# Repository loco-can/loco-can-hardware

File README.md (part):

# Loco-CAN Hardware
**Development version 3.x**

The new version 3.x marks the switch from the Atmega MCUs to the ESP32 series from the Chinese manufacturer [Espressif](https://www.espressif.com). In addition to integrated Bluetooth and WiFi functionality, the CAN controller is also already built in, making the modules even smaller.

The first module is a complete 4-quadrant motor driver for 80 amps motor current, which can be operated directly on the CAN bus.

Version 3.x is fully compatible with all other versions.

**Current version V2.2**

The software is managed in the [Loco-CAN-Software](https://github.com/Loco-can/Loco-can-software) repository.

The Loco-CAN project is an electronic control system for the large passenger-carrying garden railway. The communication is based on the CAN bus, which is used in the automotive industry and in automation. The serial signal transmission is very robust and supports multiple masters and multiple slaves.

The modular system consists of different components with specialized tasks. For example, there are modules for operating, for controlling motor controls, light switch modules or sensors for current and voltage measurement or speed values. Actuators that are addressed by a servo module can even be used to control diesel engines or gearboxes.

Due to the flexibility of the CAN bus, additional modules can easily be connected without having to change the existing structure.

The system is not only intended for networking within a traction vehicle, but can also be routed through the train via a four-pole cable. This means that not only can control consoles be connected at any point in the train, but also, for example, lights in wagons can be operated.

The system is still under developement. The CAN-specification is defined but can be extended. Board designs are available in different versions, due to the process of evolvement. Besides bugs in the board design details like the pinout of the program interface differ between the versions.

# Version
The current development of the system is based on version 2.x. It combines the microcontroller and the CAN bus connector with the specialized function on one board. Due to the use of SMD components, the modules are significantly smaller than in old 1.x versions.

With the universal module, a version with an expansion bus is also available.

## Wired units
| Unit            | Type            |
|:----------------|:----------------|
| Processor       | Atmega 328P     |
| CAN-Controller  | MCP 2515        |
| CAN-Transceiver | MCP 2551        |

## Wireless units
| Unit            | Type            |
|:----------------|:----------------|
| Processor       | ESP32           |
| CAN-Controller  | integrated      |
| CAN-Transceiver | MCP 2551        |

# Connectors
The following connectors for the basic IOs are universal used by all modules if needed. The information includes the technical specifications for the connectors and the electrical assignment.

## CAN bus
The CAN-bus is found on all modules, even the WIFI. It connects all modules and provides both communication and supply.

**4-pin 2x2**
Plug: MATE-N-LOK 794617-4
Jack: MATE-N-LOK 3-794618-4

| pin | usage                      |
|:---:|:---------------------------|
| 1   | GND                        |
| 2   | CAN-L                      |
| 3   | CAN-H                      |
| 4   | +6-30 Volt / max. 5 Ampere |

### Loco interconnection
**4-pin Mini-XLR**
The Mate-N-LOK connectors are used for internal wiring only. 4-pin MINI-XLR connectors are used to couple vehicles together. The plugs are robust, but at the same time small enough to allow model-like housings around the plugs. The pin assignment matches the internal connectors. On the vehicle the female connectors are used.

| pin | usage                      |
|:---:|:---------------------------|
| 1   | +6-30 Volt / max. 5 Ampere |
| 2   | CAN-L                      |
| 3   | CAN-H                      |
| 4   | GND                        |

### Cables
The four-pole CAN bus cables should have a minimum cross-section of 0.34mm² in order to withstand the maximum current of five amperes.

Recommended cable: UNITRONIC® ROBUST 4x0.34 black

## Pulse
Used for speed or rpm measurement.

**2-pin horizontal**
Plug: MATE-N-LOK 2-1445055-2
Jack: MATE-N-LOK 1445022-2

| pin | usage |
|:---:|:------|
| 1   | Pulse |
| 2   | GND   |

## Power
Supply input for the Loco-system.

**2-pin vertical**
Plug: MATE-N-LOK 794617-2
Jack: MATE-N-LOK 3-794618-2

| pin | usage  |
|:---:|:-------|
| 1   | +6-30V |
| 2   | GND    |

# ICP SDI pads
To flash the bootloader on Atmega chips latter versions provide four pads to access the SDI port of the MCU and a reset signal. A jumper in the CS line between the MCU and the CAN controller has to be open for the flash process and closed for normal operation.

The hardware versions with the SDI pads before 2.2 are marked with a letter s at the end of the version string.

ICP-Interface
| pin | usage |
|:----|:------|
| 1   | SCK   |
| 2   | SI    |
| 3   | SO    |
| 4   | RST   |

# Modules
All modules, except Loco-Single, are equipped with two 4-pin CAN connectors. The following modules are available or in developement:

## Interface definitions
The pinout of the FTDI interface for flashing new software differs in the early versions. The standard pinout will be implemented in all revisions, divergent pinouts are listed with the version descriptions.

All versions are compatible on the CAN-bus, the differences are only in the expansion ports.

Standard FTDI Interface to flash software updates
| pin | usage        | cable  |
|:----|:-------------|--------|
| 1   | **1 DTS**    | yellow |
| 2   | **2 RX**     | braun  |
| 3   | **3 TX**     | white  |
| 4   | **4 3V3/5V** | green  |
| 5   | **GND**      | GND    |

# Loco-Motor
With the Loco-Motor module all types of power drivers can be controlled via the CAN bus. The setup of the motor software can be adapted to a wide variety of motor control drivers. With the additional light and horn outputs a locomotive control can be set up with a control and a motor module.

## V2.1a/V2.2
The versions mainly differ in the pinout of the FDTI-interface.

### Motor driver
Plug: MATE-N-LOK 1-794617-0
Jack: MATE-N-LOK 4-794618-0

| pin | usage       | pin | usage       |
|:----|:------------|:----|:------------|
| 1   | +bus IN     | 2   | Light       |               
| 3   | DRIVE       | 4   | HORN        |
| 5   | BREAK       | 6   | MOTOR VOLT+ |
| 7   | FORWARD     | 8   | MOTOR VOLT- |
| 9   | REVERSE     | 10  | GND         |

Pins 6 and 8 are connected to the motor output to sense the voltage. Drive and break outputs provide a PWM signal to drive the power output stage.

### FTDI Interface
| V2.1a    | V2.1b     |
|:---------|:----------|
| 1 DTS    | **1 DTS** |
| 2 **TX** | **2 RX**  |
| 3 **RX** | **3 TX**  |
| 4 3V3    | **4 3V3** |
| 5 GND    | **5 GND** |

# Loco-Switch
With the switch module different lights and other devices can be switched. Each output can drive up to 3 Ampere, when using the external +bus input with the version greater V2.1. With the V2.0 only the maximum output current of the CAN-bus can be used.

## Setup
With the base setup the module is configurated to use the light messages to set the outputs. A setup to react on every message for each output increases the flexibility. As an example four outputs can be used for different lights, one output to drive a horn and the last to activate an pantograph.

###CAN light stati
The can protocol supports eight light stati in out byte, that can be mapped to the six output lines in the module setup. To activate a status, the corresponding bit has to be set to 1.

	bits     7      6      5      4      3      2      1      0
	       	main  train   cab   instr   back    high   low   posit
	       	------------------------------------------------------
	main:	main light switch
	train:	train lights
	cab:	cabine light
	instr:	instrument light
	back:	back light
	high:	bright spot light
	low:	low spot light
	posit:	position light

A common current sensor returns the overall consumption of all outputs.

The versions differ in the pinout of the output connector and the FDTI-interface.

## Output connector
Degson DG308-2.54-08P-14-00AH
or
JST XH

## Hardware version V2.0
| pin | usage      |
|:----|:-----------|
| 1   | Output 1   |
| 2   | Output 2   |
| 3   | Output 3   |
| 4   | Output 4   |
| 5   | Output 5   |
| 6   | Output 6   |
| 7   | GND        |

## Hardware version V2.1a/V2.2
| pin | usage      |
|:----|:-----------|
| 1   | +bus       |
| 2   | Output 1   |
| 3   | Output 2   |
| 4   | Output 3   |
| 5   | Output 4   |
| 6   | Output 5   |
| 7   | Output 6   |
| 8   | GND        |

The switching module can switch up to 3 amps per output. Both resistive and inductive loads can be switched. If the current is taken from the bus, make sure that the total consumption of the system does not exceed the limit of 5 amperes.

If all outputs are operated with 3 amps, a separate supply line must be laid from the positive pole of the battery to the loads and from the negative pole of the battery to the GND connection of the switching output. The value of the maximum current must be adjusted in the configuration of the module.

### FTDI Interface
| V2.1     | V2.1a     |
|:---------|:----------|
| 1 DTS    | **1 DTS** |
| 2 **TX** | **2 RX**  |
| 3 **RX** | **3 TX**  |
| 4 3V3    | **4 3V3** |
| 5 GND    | **5 GND** |

# Loco-Single
A tiny module with only one fix wired CAN connector and one current controlled output for a single LED light. It can be used for intelligent back lights. In this case, a backlight heartbeat status can detect the train integrity.

# Loco-Sensor
The sendor module provides four voltage inputs and a current measurement up to 30 Ampere. In addition a speed/pulse input is provided.

## Hardware version V2.1/V2.1a/V2.1a-s
The versions differ in the pinout of the FDTI-interface. Both versions V2.1a and V2.1a-s offers the SDI pads.

### Voltage
The pins can provide absolute values reffered to GND, or relative values between two pins, depending on the module setup.

| pin | usage     |
|:----|:----------|
| 1   | Voltage 1 |
| 2   | Voltage 2 |
| 3   | Voltage 3 |
| 4   | Voltage 4 |

### Current
The current measurement connectors are thwo 6mm holes outside of the casing. The direction of the current is provided as positive or negative values. The ratio of the positive direction to the connection on the pins, can be set in the setup.

### Speed/pulse
See in the Connector section below.

### FTDI Interface
| V2.1     | V2.1a     |
|:---------|:----------|
| 1 DTS    | **1 DTS** |
| 2 **TX** | **2 RX**  |
| 3 **RX** | **3 TX**  |
| 4 3V3    | **4 3V3** |
| 5 GND    | **5 GND** |

## Loco-Servo
The module provides four analog model servo outputs. The power for all servos must not exceed 900mA. If more power is needed, the 5 Volt for the servo motors must be supplied by an external voltage regulator.

The values for each servo motor position can be mapped to each analog value of CAN messages. The received values are mapped using input min and max settings and output min and max values. Reverse actions are reached by setting the output mapping values in a reversed order (forward: input 0-1024 => output 100-170, reverse: input 0-1024 => output: 180-100).

### V2.0/V2.2
The versions only differ in the pinout of the FDTI-interface.

### 12-pin Servo Output
Plug: MATE-N-LOK 1-794617-2
Jack: MATE-N-LOK 4-794618-2

| Row 1     | Row 2      |
|:----------|:-----------|
| 1 Servo-1 | 7 Servo-3  |
| 2 +5V     | 8 +5V      |
| 3 GND     | 9 GND      |
| 4 Servo-2 | 10 Servo-4 |
| 5 +5V     | 11 +5V     |
| 6 GND     | 12 GND     |

### FTDI Interface
| V2.0     | V2.2  |
|:---------|:----------|
| 1 DTS    | **1 DTS** |
| 2 **TX** | **2 RX**  |
| 3 **RX** | **3 TX**  |
| 4 3V3    | **4 3V3** |
| 5 GND    | **5 GND** |

## Loco-Universal
These modules offer an unallocated connector for universal use. 

### V1.0
The first prototype board using DIL packages and JST-PH connectors for the CAN-bus. **Although this version is compatible with the system, it is no longer supported!**

**Extension bus: 10x1 pins**
| pin         | usage        |
|:------------|:-------------|
| 1  VCC      |              |
| 2  D9 (PWM) | METER_AMP    |
| 3  D8       | METER_VOLT   |
| 4  D7       | STATUS_GREEN |
| 5  D6 (PWM) | STATUS_RED   |
| 6  A0       | ANALOG_DRIVE |
| 7  A1       | MAINS_SWITCH |
| 8  A2       | DIR_SWITCH   |
| 9  A3       | LIGHT_SWITCH |
| 10 GND      |              |

### V1.2
The second prototype board using DIL packages and an bigger extension bus. It was never produced. **Although this version is compatible with the system, it is no longer supported!**

**Extension bus: 8x2 pins**
| pin         | usage             | pin         | usage              |
|:------------|:------------------|:------------|:-------------------|
| 1  VCC      |                   | 2  D2       |                    | 
| 3  A5       |                   | 4  D3 (PWM) |                    |
| 5  A4       |                   | 6  D4       |                    |
| 7  A3       |                   | 8  D5 (PWM) |                    |
| 8  A2       |                   | 10 D6 (PWM) | STATUS_RED         |
| 11 A1       |                   | 12 D7       | STATUS_GREEN       |
| 13 A0       |                   | 14 D8       | METER_VOLT (Servo) |
| 15 D9 (PWM) | METER_AMP (Servo) | 16 GND      |                    |

**big extension bus version: 9x2 pins**
| pin         | usage             | pin         | usage              |
|:------------|:------------------|:------------|:-------------------|
| 17  +bus    |                   | 18 GND      |                    | 

### FTDI Interface
Both versions provide the default FTDI pinout.
| pin | usage     |
|:----|:----------|
| 1   | **1 DTS** |
| 2   | **2 RX**  |
| 3   | **3 TX**  |
| 4   | **4 3V3** |
| 5   | **GND**   |

### V2.x
From version 2.x the universal board is pin compatible with the WIFI universal board.

| **IO 1**           | **IO 2**             |
|:-------------------|:---------------------|
| **9x1 pins**       | **5+4x1 pins**       |
| 1 +5V              | 1 +bus               |
| 2 D2               | 2 A5                 |
| 3 D3               | 3 A4                 |
| 4 D4               | 4 A3                 |
| 5 D5               | 5 A2                 |
| 6 D6               |                      |
| 7 D7               | 1 A1                 |
| 8 D8               | 2 A0                 |
| 9 GND              | 3 D9                 |
|                    | 4 GND                |

### FTDI Interface
The version provide the default FTDI pinout. To flash a new software version, pin 3 of the 5-pin IO 2 must be connected to GND before power up.

| pin | usage     |
|:----|:----------|
| 1   | **1 DTS** |
| 2   | **2 RX**  |
| 3   | **3 TX**  |
| 4   | **4 3V3** |
| 5   | **GND**   |

The +bus connection can either be used to power the CAN bus from an outside source, like a motor driver or in reverse provide an outside device with the bus supply of 6 to 30 Volts. In the different use cases the diode D2 has to be swapped regarding the printed direction for in or out on the pcb.

## Loco-WIFI (universal)
The Loco-WIFI is a universal module with two extension busses besides the two CAN connectors. It can establish a wireless connection via WIFI and Bluetooth. 

### V2.1
The ESP32 boards are shipped with a bootloader and do not need the SPI flash pads.

| **IO 1**           | **IO 2**             |
|:-------------------|:---------------------|
| **9x1 pins**       | **5+4x1 pins**       |
| 1 +3,3V            | 1 VCC (12V)          |
| 2 IO27             | 2 IO4                |
| 3 IO26             | 3 IO0 (GND to Flash) |
| 4 IO25             | 4 IO2                |
| 5 IO33             | 5 IO15               |
| 6 IO32             |                      |
| 7 IO35             | 1 IO13               |
| 8 IO34             | 2 IO12               |
| 9 GND              | 3 IO14               |
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
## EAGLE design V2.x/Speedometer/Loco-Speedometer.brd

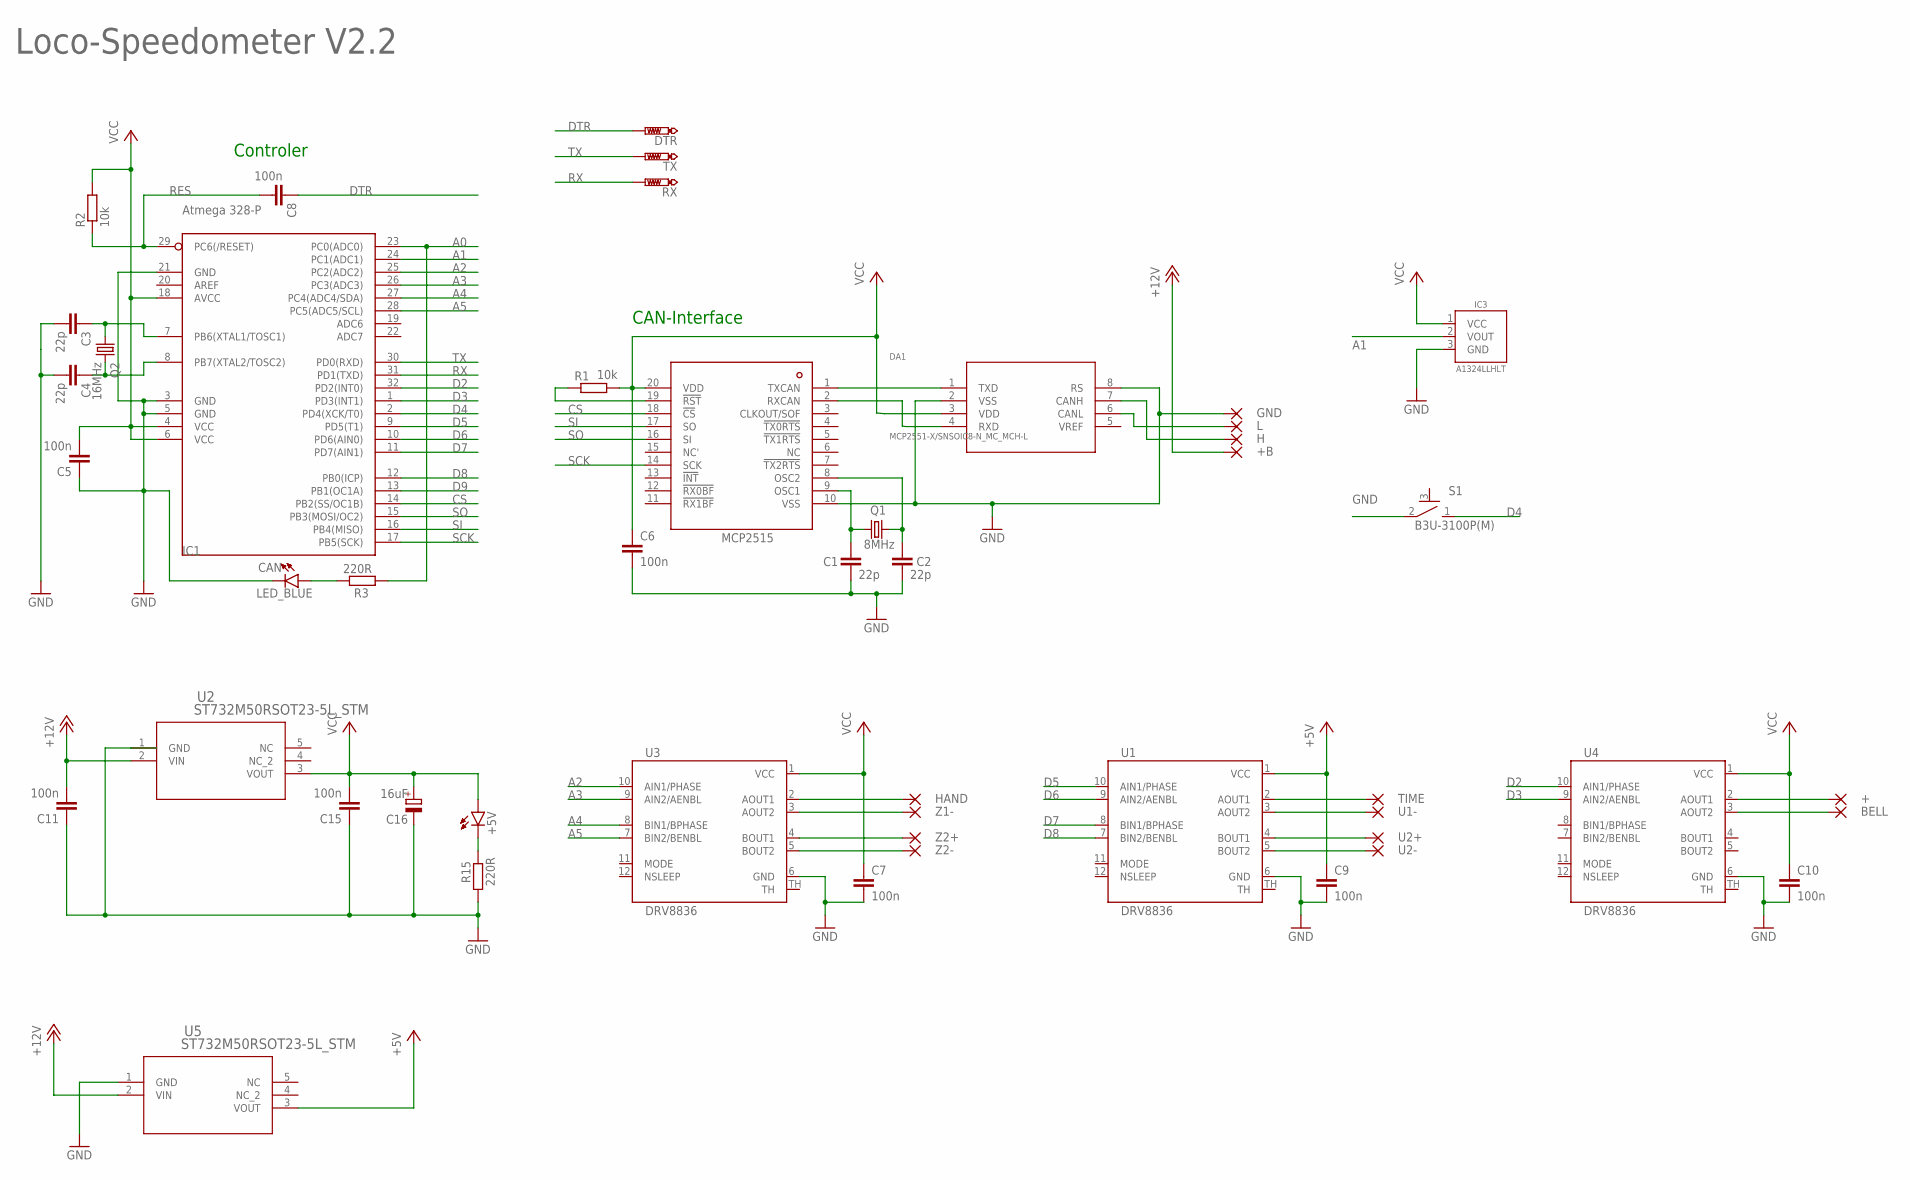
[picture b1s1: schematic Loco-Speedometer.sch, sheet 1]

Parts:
+: SMD1; SMD1,27-1,90
+5V: LEDCHIP-LED0603; CHIP-LED0603
+B: SMD1; SMD1,27-1,90
BELL: SMD1; SMD1,27-1,90
C1, C2, C3, C4: 22p; C0402K
C5, C6, C7, C8, C9, C10, C11, C15: 100n; C0402K
C16: 16uF; A/3216-18W
CAN: LED_BLUE; LEDC1608X39N_B
DA1: MCP2551-X/SNSOIC8-N_MC_MCH-L; SOIC8-N_MC_MCH-L
DTR: PTR1B1,27; B1,27
GND: SMD1; SMD1,27-1,90
H: SMD1; SMD1,27-1,90
HAND: SMD1; SMD1,27-1,90
IC1: Atmega 328-P; TQFP32-08
IC2: MCP2515; TSSOP20
IC3: A1324LLHLT; SOT95P285X113-3N
L: SMD1; SMD1,27-1,90
Q1: 8MHz; 5.0X3.2_2
Q2: 16MHz; 5.0X3.2_2
R1, R2: 10k; R0402
R3, R15: 220R; R0402
RX: PTR1B1,27; B1,27
S1: B3U-3100P(M)
TIME: SMD1; SMD1,27-1,90
TX: PTR1B1,27; B1,27
U1, U3, U4: DRV8836; 12WSON
U1-, U2+, U2-: SMD1; SMD1,27-1,90
U2, U5: ST732M50RSOT23-5L_STM; SOT23-5L_STM
Z1-, Z2+, Z2-: SMD1; SMD1,27-1,90

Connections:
+5V: C9.1, U1.1 (VCC), U5.3 (VOUT)
+12V: +B.1, C11.2, U2.2 (VIN), U5.2 (VIN)
A0: IC1.23 (PC0(ADC0)), R3.1
A1: IC1.24 (PC1(ADC1)), IC3.2 (VOUT)
A2: IC1.25 (PC2(ADC2)), U3.10 (AIN1/PHASE)
A3: IC1.26 (PC3(ADC3)), U3.9 (AIN2/AENBL)
A4: IC1.27 (PC4(ADC4/SDA)), U3.8 (BIN1/BPHASE)
A5: IC1.28 (PC5(ADC5/SCL)), U3.7 (BIN2/BENBL)
CAN-H: DA1.7 (CANH), H.1
CAN-L: DA1.6 (CANL), L.1
CAN-OCC1: C1.1, IC2.9 (OSC1), Q1.1
CAN-OCC2: C2.1, IC2.8 (OSC2), Q1.2
CS: IC1.14 (PB2(SS/OC1B)), IC2.18 (!CS)
D2: IC1.32 (PD2(INT0)), U4.10 (AIN1/PHASE)
D3: IC1.1 (PD3(INT1)), U4.9 (AIN2/AENBL)
D4: IC1.2 (PD4(XCK/T0)), S1.1 (2)
D5: IC1.9 (PD5(T1)), U1.10 (AIN1/PHASE)
D6: IC1.10 (PD6(AIN0)), U1.9 (AIN2/AENBL)
D7: IC1.11 (PD7(AIN1)), U1.8 (BIN1/BPHASE)
D8: IC1.12 (PB0(ICP)), U1.7 (BIN2/BENBL)
D9: IC1.13 (PB1(OC1A))
DTR: C8.1, DTR.TP
GND: C1.2, C2.2, C3.2, C4.2, C5.1, C6.2, C7.2, C9.2, C10.2, C11.1, C15.1, C16.-, CAN.1 (C), DA1.2 (VSS), DA1.8 (RS), GND.1, IC1.3 (GND), IC1.5 (GND), IC1.21 (GND), IC2.10 (VSS), IC3.3 (GND), R15.1, S1.2 (1), U1.6 (GND), U2.1 (GND), U3.6 (GND), U4.6 (GND), U5.1 (GND)
unnamed: CAN.2 (A), R3.2
unnamed: IC2.19 (!RST), R1.1
unnamed: C7.1, U3.1 (VCC)
unnamed: C3.1, IC1.7 (PB6(XTAL1/TOSC1)), Q2.1
unnamed: C4.1, IC1.8 (PB7(XTAL2/TOSC2)), Q2.2
unnamed: +5V.C, R15.2
RES: C8.2, IC1.29 (PC6(/RESET)), R2.1
RX: IC1.31 (PD1(TXD)), RX.TP
RXCAN: DA1.4 (RXD), IC2.2 (RXCAN)
SCK: IC1.17 (PB5(SCK)), IC2.14 (SCK)
SI: IC1.16 (PB4(MISO)), IC2.17 (SO)
SO: IC1.15 (PB3(MOSI/OC2)), IC2.16 (SI)
TX: IC1.30 (PD0(RXD)), TX.TP
TXCAN: DA1.1 (TXD), IC2.1 (TXCAN)
U1+: TIME.1, U1.2 (AOUT1)
U1+1: +.1, U4.2 (AOUT1)
U1-: U1.3 (AOUT2), U1-.1
U1-1: BELL.1, U4.3 (AOUT2)
U2+: U1.4 (BOUT1), U2+.1
U2-: U1.5 (BOUT2), U2-.1
VCC: +5V.A, C5.2, C6.1, C10.1, C15.2, C16.+, DA1.3 (VDD), IC1.4 (VCC), IC1.6 (VCC), IC1.18 (AVCC), IC2.20 (VDD), IC3.1 (VCC), R1.2, R2.2, U2.3 (VOUT), U4.1 (VCC)
Z1+: HAND.1, U3.2 (AOUT1)
Z1-: U3.3 (AOUT2), Z1-.1
Z2+: U3.4 (BOUT1), Z2+.1
Z2-: U3.5 (BOUT2), Z2-.1

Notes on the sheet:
CAN-Interface
Controler
Loco-Speedometer V2.2

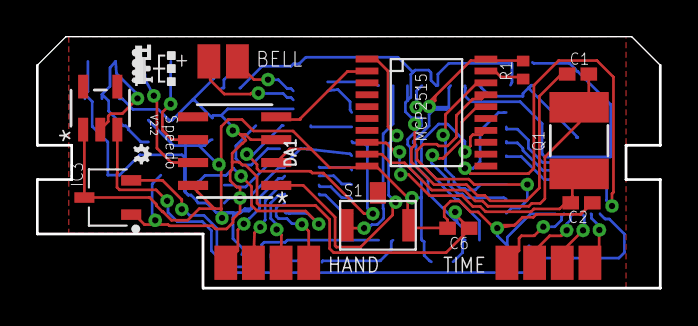
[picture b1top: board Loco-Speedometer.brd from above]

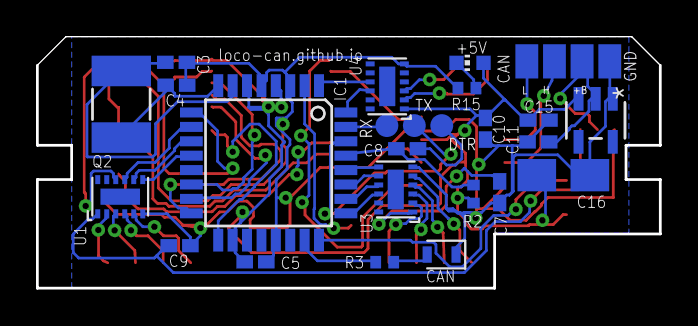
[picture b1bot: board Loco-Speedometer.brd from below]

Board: 2 copper layers, 34.6 x 14.0 mm, 48 parts (28 on the bottom side), 47 nets.

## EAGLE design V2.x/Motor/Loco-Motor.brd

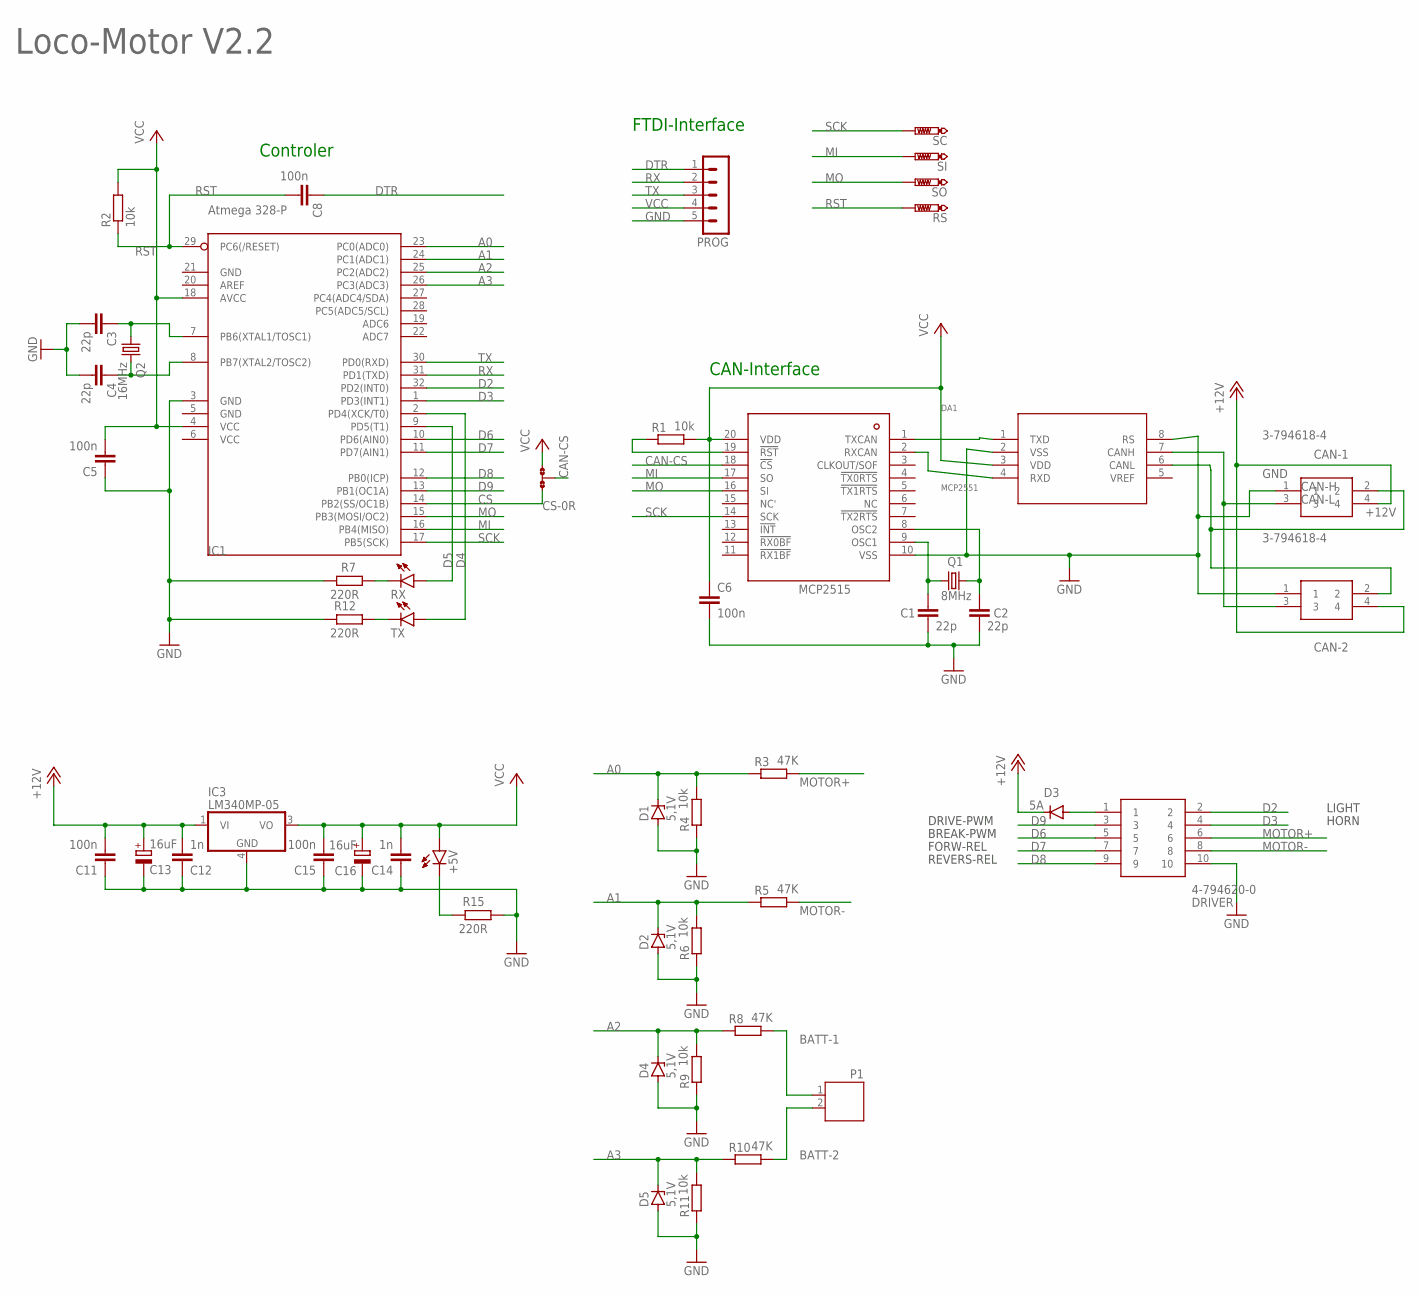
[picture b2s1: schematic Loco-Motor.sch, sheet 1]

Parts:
+5V: LEDCHIP-LED0603; CHIP-LED0603
C1, C2, C3, C4: 22p; C0402K
C5, C6, C8, C11, C15: 100n; C0402K
C12, C14: 1n; C0402K
C13, C16: 16uF; A/3216-18W
CAN-1, CAN-2: 3-794618-4
CS: 0R-JUMPA; A0R-JMP
D1, D2, D4, D5: 5,1V; SOD80C
D3: 5A; DO214AA
DA1: MCP2551; SOIC8-N_MC_MCH
DRIVER: 4-794620-0; 47946200
IC1: Atmega 328-P; TQFP32-08
IC2: MCP2515; TSSOP20
IC3: LM340MP-05; SOT223
P1: JST-PH2
PROG: MA05-1
Q1: 8MHz; HC49/S
Q2: 16MHz; HC49/S
R1, R2: 10k; R0805
R3, R5, R8, R10: 47K; MINI_MELF-0102W
R4, R6, R9, R11: 10k; MINI_MELF-0102W
R7, R12, R15: 220R; R0805
RS: PTR1B1,27; B1,27
RX: LEDCHIP-LED0603; CHIP-LED0603
SC: PTR1B1,27; B1,27
SI: PTR1B1,27; B1,27
SO: PTR1B1,27; B1,27
TX: LEDCHIP-LED0603; CHIP-LED0603

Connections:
+12V: C11.2, C12.2, C13.+, CAN-1.4, CAN-2.4, D3.C, IC3.1 (VI)
A0: D1.C, IC1.23 (PC0(ADC0)), R3.1, R4.2
A1: D2.C, IC1.24 (PC1(ADC1)), R5.1, R6.2
A2: D4.C, IC1.25 (PC2(ADC2)), R8.1, R9.2
A3: D5.C, IC1.26 (PC3(ADC3)), R10.1, R11.2
BATT-1: P1.1, R8.2
BATT-2: P1.2, R10.2
CAN-CS: CS.2, IC2.18 (!CS)
CAN-H: CAN-1.3, CAN-2.3, DA1.7 (CANH)
CAN-L: CAN-1.2, CAN-2.2, DA1.6 (CANL)
CAN-OCC1: C1.1, IC2.9 (OSC1), Q1.1
CAN-OCC2: C2.1, IC2.8 (OSC2), Q1.2
CS: CS.3, IC1.14 (PB2(SS/OC1B))
D2: DRIVER.2, IC1.32 (PD2(INT0))
D3: DRIVER.4, IC1.1 (PD3(INT1))
D4: IC1.2 (PD4(XCK/T0)), TX.A
D5: IC1.9 (PD5(T1)), RX.A
D6: DRIVER.5, IC1.10 (PD6(AIN0))
D7: DRIVER.7, IC1.11 (PD7(AIN1))
D8: DRIVER.9, IC1.12 (PB0(ICP))
D9: DRIVER.3, IC1.13 (PB1(OC1A))
DTR: C8.1, PROG.1
GND: C1.2, C2.2, C3.2, C4.2, C5.1, C6.2, C11.1, C12.1, C13.-, C14.1, C15.1, C16.-, CAN-1.1, CAN-2.1, D1.A, D2.A, D4.A, D5.A, DA1.2 (VSS), DA1.8 (RS), DRIVER.10, IC1.3 (GND), IC1.5 (GND), IC1.21 (GND), IC2.10 (VSS), IC3.4 (GND), PROG.5, R4.1, R6.1, R7.2, R9.1, R11.1, R12.2, R15.1
MI: IC1.16 (PB4(MISO)), IC2.17 (SO), SI.TP
MO: IC1.15 (PB3(MOSI/OC2)), IC2.16 (SI), SO.TP
MOTOR+: DRIVER.6, R3.2
MOTOR-: DRIVER.8, R5.2
unnamed: D3.A, DRIVER.1
unnamed: R7.1, RX.C
unnamed: R12.1, TX.C
unnamed: IC2.19 (!RST), R1.1
unnamed: C3.1, IC1.7 (PB6(XTAL1/TOSC1)), Q2.1
unnamed: C4.1, IC1.8 (PB7(XTAL2/TOSC2)), Q2.2
unnamed: +5V.C, R15.2
RST: C8.2, IC1.29 (PC6(/RESET)), R2.1, RS.TP
RX: IC1.31 (PD1(TXD)), PROG.2
RXCAN: DA1.4 (RXD), IC2.2 (RXCAN)
SCK: IC1.17 (PB5(SCK)), IC2.14 (SCK), SC.TP
TX: IC1.30 (PD0(RXD)), PROG.3
TXCAN: DA1.1 (TXD), IC2.1 (TXCAN)
VCC: +5V.A, C5.2, C6.1, C14.2, C15.2, C16.+, CS.1, DA1.3 (VDD), IC1.4 (VCC), IC1.6 (VCC), IC1.18 (AVCC), IC2.20 (VDD), IC3.3 (VO), PROG.4, R1.2, R2.2

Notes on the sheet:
FTDI-Interface
CAN-Interface
Controler
DRIVE-PWM
BREAK-PWM
LIGHT
FORW-REL
REVERS-REL
HORN
Loco-Motor V2.2

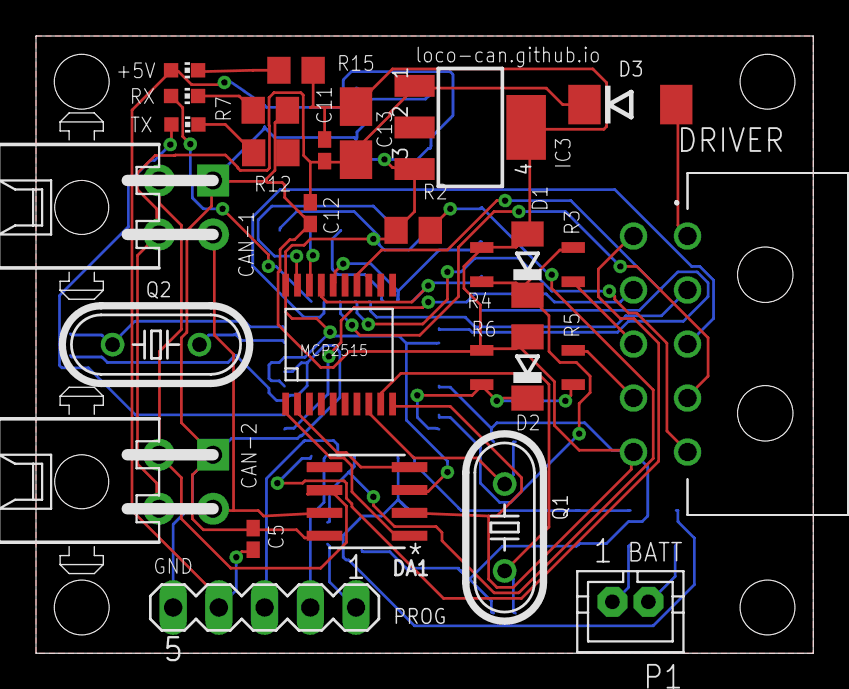
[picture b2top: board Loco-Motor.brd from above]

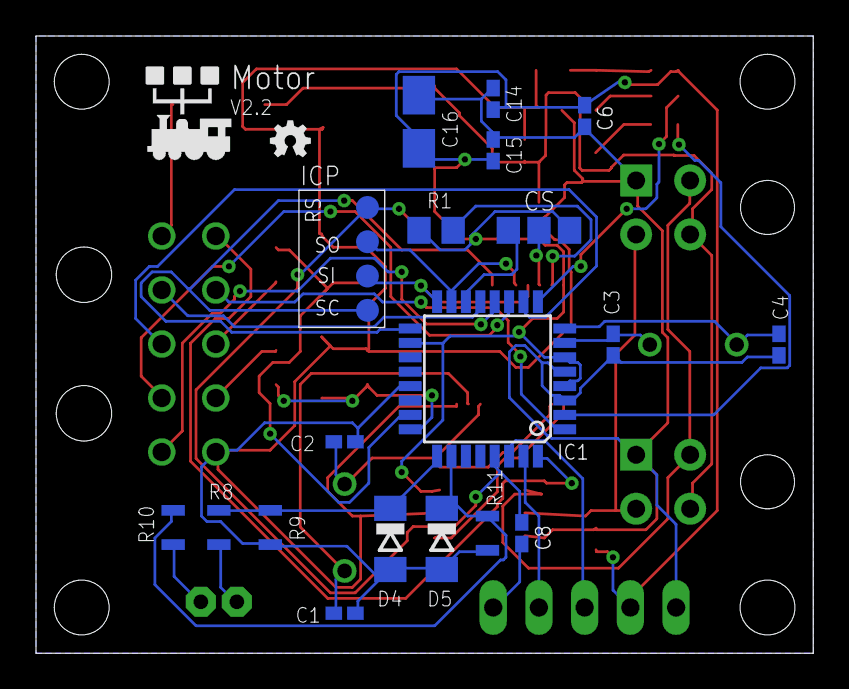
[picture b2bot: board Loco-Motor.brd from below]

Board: 2 copper layers, 43.2 x 34.3 mm, 50 parts (22 on the bottom side), 41 nets.

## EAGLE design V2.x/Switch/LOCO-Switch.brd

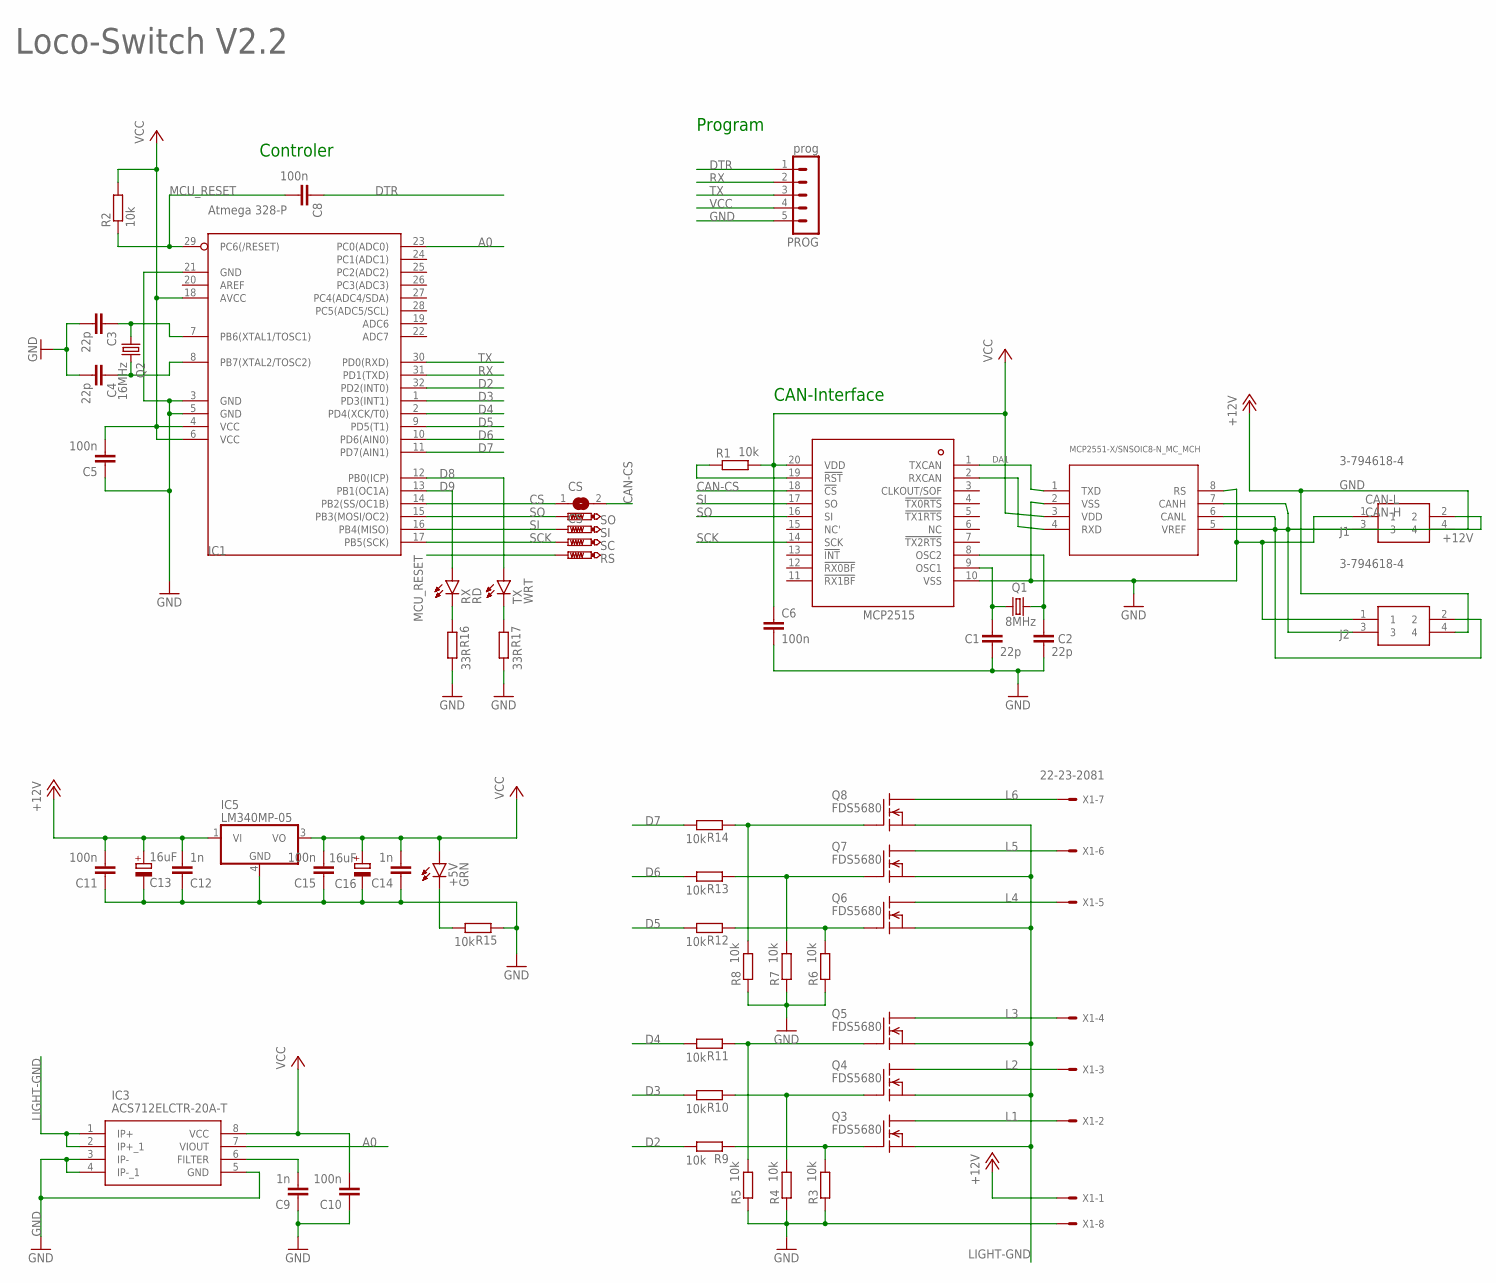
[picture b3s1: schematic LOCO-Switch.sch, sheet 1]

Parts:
+5V: GRN; CHIP-LED0603
C1, C2, C3, C4: 22p; C0402K
C5, C6, C8, C10, C11, C15: 100n; C0402K
C9, C12, C14: 1n; C0402K
C13, C16: 16uF; A/3216-18W
CS: CS; SJ
DA1: MCP2551-X/SNSOIC8-N_MC_MCH; SOIC8-N_MC_MCH
IC1: Atmega 328-P; TQFP32-08
IC2: MCP2515; TSSOP20
IC3: ACS712ELCTR-20A-T; SOIC127P600X175-8N
IC5: LM340MP-05; SOT223
J1, J2: 3-794618-4
PROG: prog; MA05-1
Q1: 8MHz; HC49/S
Q2: 16MHz; HC49/S
Q3, Q4, Q5, Q6, Q7, Q8: FDS5680; SO-8
R1, R2, R3, R4, R5, R6, R7, R8, R9, R10, R11, R12, R13, R14, R15: 10k; R0603
R16, R17: 33R; R0603
RS: PTR1B1,27; B1,27
RX: RD; CHIP-LED0603
SC: PTR1B1,27; B1,27
SI: PTR1B1,27; B1,27
SO: PTR1B1,27; B1,27
TX: WRT; CHIP-LED0603
X1: 22-23-2081

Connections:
+12V: C11.2, C12.2, C13.+, IC5.1 (VI), J1.4, J2.4, X1.1
A0: IC1.23 (PC0(ADC0)), IC3.7 (VIOUT)
CAN-CS: CS.2, IC2.18 (!CS)
CAN-H: DA1.7 (CANH), J1.3, J2.3
CAN-L: DA1.5 (VREF), DA1.6 (CANL), J1.2, J2.2
CAN-OCC1: C1.1, IC2.9 (OSC1), Q1.1
CAN-OCC2: C2.1, IC2.8 (OSC2), Q1.2
CS: CS.1, IC1.14 (PB2(SS/OC1B))
D2: IC1.32 (PD2(INT0)), R9.2
D3: IC1.1 (PD3(INT1)), R10.2
D4: IC1.2 (PD4(XCK/T0)), R11.2
D5: IC1.9 (PD5(T1)), R12.2
D6: IC1.10 (PD6(AIN0)), R13.2
D7: IC1.11 (PD7(AIN1)), R14.2
D9: IC1.13 (PB1(OC1A)), RX.A
DTR: C8.1, PROG.1
GND: C1.2, C2.2, C3.2, C4.2, C5.1, C6.2, C9.1, C10.1, C11.1, C12.1, C13.-, C14.1, C15.1, C16.-, DA1.2 (VSS), DA1.8 (RS), IC1.3 (GND), IC1.5 (GND), IC1.21 (GND), IC2.10 (VSS), IC3.3 (IP-), IC3.4 (IP-_1), IC3.5 (GND), IC5.4 (GND), J1.1, J2.1, PROG.5, R3.1, R4.1, R5.1, R6.1, R7.1, R8.1, R15.1, R16.2, R17.2, X1.8
L1: Q3.5 (D), Q3.6 (D), Q3.7 (D), Q3.8 (D), X1.2
L2: Q4.5 (D), Q4.6 (D), Q4.7 (D), Q4.8 (D), X1.3
L3: Q5.5 (D), Q5.6 (D), Q5.7 (D), Q5.8 (D), X1.4
L4: Q6.5 (D), Q6.6 (D), Q6.7 (D), Q6.8 (D), X1.5
L5: Q7.5 (D), Q7.6 (D), Q7.7 (D), Q7.8 (D), X1.6
L6: Q8.5 (D), Q8.6 (D), Q8.7 (D), Q8.8 (D), X1.7
LIGHT-GND: IC3.1 (IP+), IC3.2 (IP+_1), Q3.1 (S), Q3.2 (S), Q3.3 (S), Q4.1 (S), Q4.2 (S), Q4.3 (S), Q5.1 (S), Q5.2 (S), Q5.3 (S), Q6.1 (S), Q6.2 (S), Q6.3 (S), Q7.1 (S), Q7.2 (S), Q7.3 (S), Q8.1 (S), Q8.2 (S), Q8.3 (S)
MCU_RESET: C8.2, IC1.29 (PC6(/RESET)), R2.1, RS.TP
unnamed: C9.2, IC3.6 (FILTER)
unnamed: Q3.4 (G), R3.2, R9.1
unnamed: Q4.4 (G), R4.2, R10.1
unnamed: Q5.4 (G), R5.2, R11.1
unnamed: Q6.4 (G), R6.2, R12.1
unnamed: IC2.19 (!RST), R1.1
unnamed: Q7.4 (G), R7.2, R13.1
unnamed: Q8.4 (G), R8.2, R14.1
unnamed: R16.1, RX.C
unnamed: C3.1, IC1.7 (PB6(XTAL1/TOSC1)), Q2.1
unnamed: C4.1, IC1.8 (PB7(XTAL2/TOSC2)), Q2.2
unnamed: +5V.C, R15.2
unnamed: R17.1, TX.C
unnamed: IC1.12 (PB0(ICP)), TX.A
RX: IC1.31 (PD1(TXD)), PROG.2
RXCAN: DA1.4 (RXD), IC2.2 (RXCAN)
SCK: IC1.17 (PB5(SCK)), IC2.14 (SCK), SC.TP
SI: IC1.16 (PB4(MISO)), IC2.17 (SO), SI.TP
SO: IC1.15 (PB3(MOSI/OC2)), IC2.16 (SI), SO.TP
TX: IC1.30 (PD0(RXD)), PROG.3
TXCAN: DA1.1 (TXD), IC2.1 (TXCAN)
VCC: +5V.A, C5.2, C6.1, C10.2, C14.2, C15.2, C16.+, DA1.3 (VDD), IC1.4 (VCC), IC1.6 (VCC), IC1.18 (AVCC), IC2.20 (VDD), IC3.8 (VCC), IC5.3 (VO), PROG.4, R1.2, R2.2

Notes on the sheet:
Program
CAN-Interface
Controler
Loco-Switch V2.2

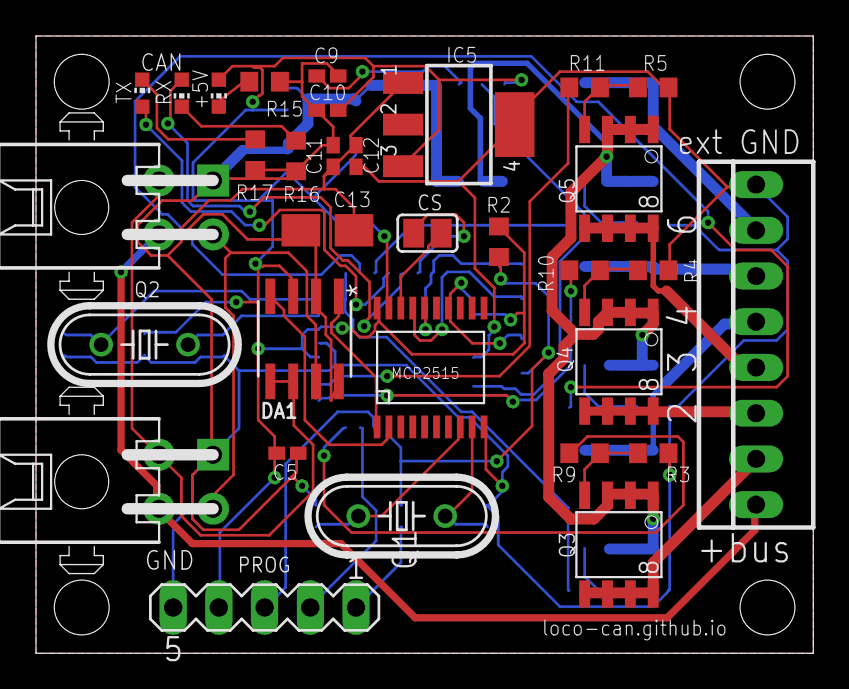
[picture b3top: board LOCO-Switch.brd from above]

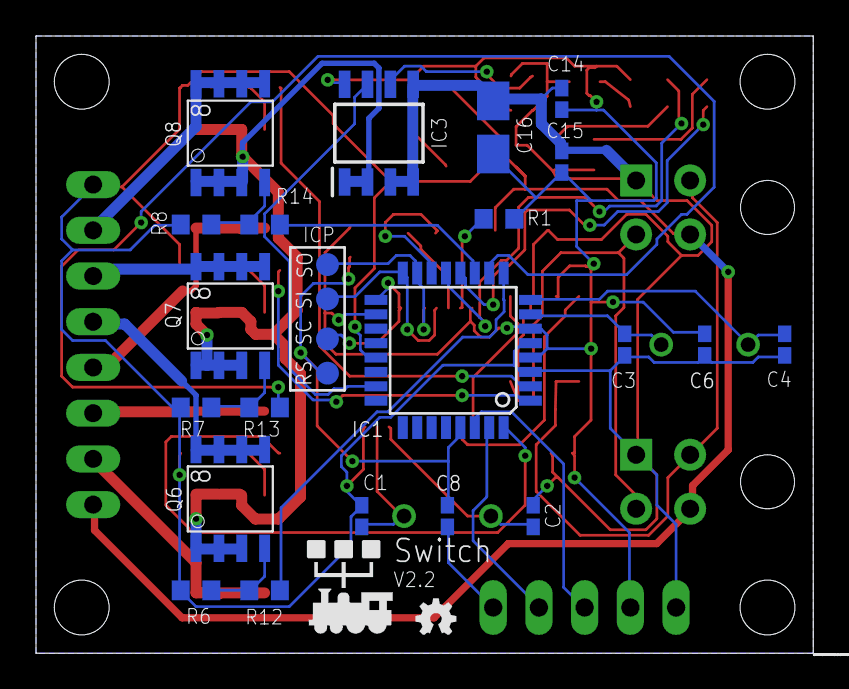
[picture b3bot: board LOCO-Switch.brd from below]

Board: 2 copper layers, 43.2 x 34.3 mm, 57 parts (25 on the bottom side), 47 nets.

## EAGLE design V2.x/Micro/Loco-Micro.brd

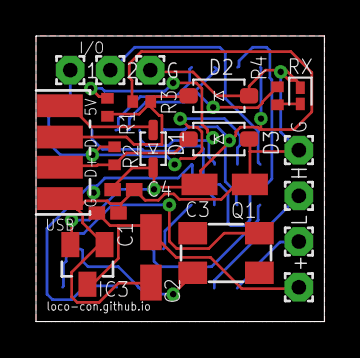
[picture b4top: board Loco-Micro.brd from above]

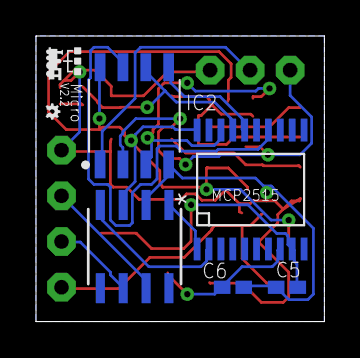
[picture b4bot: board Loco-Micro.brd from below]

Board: 2 copper layers, 16.0 x 15.9 mm, 30 parts (5 on the bottom side), 19 nets.

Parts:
1, 2: 1,6/0,8
+: 1,6/0,8
+5V: SMD1,27-2,54
-: 1,6/0,8
C1, C4: 100n; C0402K
C2, C3: 4m7; CT3216
C5, C6: 22n; C0402K
D1: 1N4148WS; SOD-323
D2, D3: MMSZ5242B-E3-18; SOD-123
D+: SMD1,27-2,54
D-: SMD1,27-2,54
G: 1,6/0,8
GND: SMD1,27-2,54
H: 1,6/0,8
IC2: ATtiny25-20SSH; SOIC127P600X175-8N
IC3: MCP1703CB; SOT23
L: 1,6/0,8
Q1: 5.0X3.2_KX-9A
R1, R2, R3, R4: R0402
RX: LED_BLUE; LEDC1005X25N_FLAT-B
U1: SOIC8-N_MC_MCH-L
U$2: MCP2515; TSSOP20

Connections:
+12V: +.1, C1.1, C2.+, IC3.3
CS: IC2.3, R1.2, U$2.18
GND: -.1, C1.2, C2.-, C3.-, C4.2, C5.2, C6.2, D2.A, D3.A, G.1, GND.1, IC2.4, IC3.1, RX.C, U1.2
IO1: 1.1, IC2.2, R2.2
IO2: 2.1, IC2.1
unnamed: C6.1, Q1.3, U$2.8
unnamed: R4.1, RX.A
unnamed: U1.1, U$2.1
unnamed: U1.4, U$2.2
unnamed: H.1, U1.7
unnamed: L.1, U1.6
unnamed: C5.1, Q1.1, U$2.9
SCK: IC2.7, U$2.14
SI: IC2.5, U$2.16
SO: IC2.6, R4.2, U$2.17
USB_5V: +5V.1, D1.A
USB_D+: D3.C, D+.1, R2.1
USB_D-: D2.C, D-.1, R1.1, R3.1
VCC: C3.+, C4.1, D1.C, IC2.8, IC3.2, R3.2, U1.3, U$2.20

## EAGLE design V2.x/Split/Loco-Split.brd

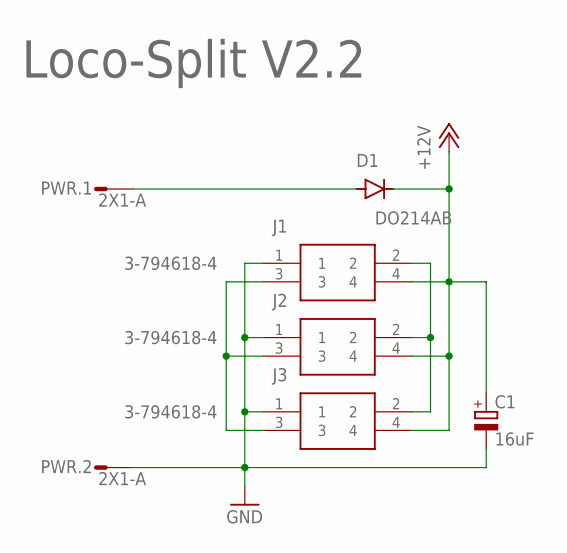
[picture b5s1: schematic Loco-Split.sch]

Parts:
C1: 16uF; A/3216-18W
D1: DO214AB; DO214AC
J1, J2, J3: 3-794618-4
PWR: 2X1-A; 3-794618-2

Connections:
+12V: C1.+, D1.C, J1.4, J2.4, J3.4
GND: C1.-, J1.1, J2.1, J3.1, PWR.2
unnamed: D1.A, PWR.1
unnamed: J1.3, J2.3, J3.3
unnamed: J1.2, J2.2, J3.2

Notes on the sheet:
Loco-Split V2.2

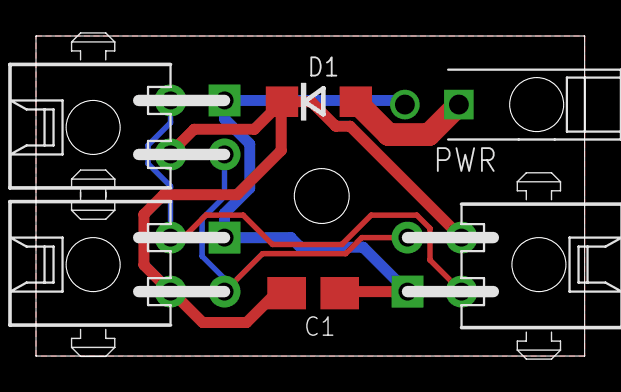
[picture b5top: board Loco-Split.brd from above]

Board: 2 copper layers, 30.5 x 17.8 mm, 6 parts (0 on the bottom side), 5 nets.

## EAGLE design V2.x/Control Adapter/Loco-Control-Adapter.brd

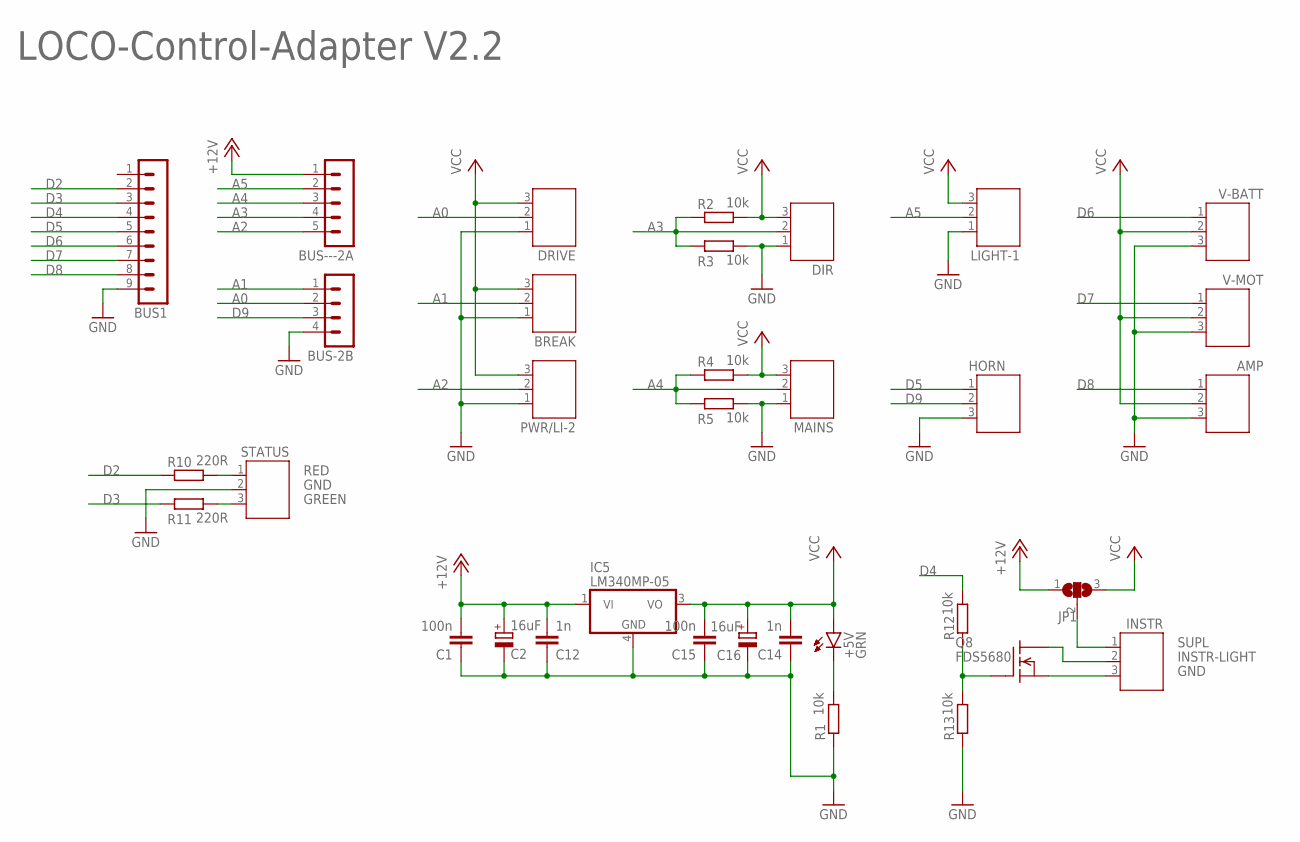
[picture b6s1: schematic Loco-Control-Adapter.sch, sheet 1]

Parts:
+5V: GRN; CHIP-LED0603
AMP: JST-PH3
BREAK: JST-PH3
BUS1: MA09-1
BUS-2B: MA04-1
BUS---2A: MA05-1
C1, C15: 100n; C0402K
C2, C16: 16uF; A/3216-18W
C12, C14: 1n; C0402K
DIR: JST-PH3
DRIVE: JST-PH3
HORN: JST-PH3
IC5: LM340MP-05; SOT223
INSTR: JST-PH3
JP1: SJ2W; SJ_2
LIGHT-1: JST-PH3
MAINS: JST-PH3
PWR/LI-2: JST-PH3
Q8: FDS5680; SO-8
R1, R12, R13: 10k; R0603
R2, R3, R4, R5: 10k; R0805
R10, R11: 220R; R0805
STATUS: JST-PH3
V-BATT: JST-PH3
V-MOT: JST-PH3

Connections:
+12V: BUS---2A.1, C1.2, C2.+, C12.2, IC5.1 (VI), JP1.1
A0: BUS-2B.2, DRIVE.2
A1: BREAK.2, BUS-2B.1
A2: BUS---2A.5, PWR/LI-2.2
A3: BUS---2A.4, DIR.2, R2.1, R3.1
A4: BUS---2A.3, MAINS.2, R4.1, R5.1
A5: BUS---2A.2, LIGHT-1.2
D2: BUS1.2, R10.1
D3: BUS1.3, R11.1
D4: BUS1.4, R12.2
D5: BUS1.5, HORN.1
D6: BUS1.6, V-BATT.1
D7: BUS1.7, V-MOT.1
D8: AMP.1, BUS1.8
D9: BUS-2B.3, HORN.2
GND: AMP.3, BREAK.1, BUS1.9, BUS-2B.4, C1.1, C2.-, C12.1, C14.1, C15.1, C16.-, DIR.1, DRIVE.1, HORN.3, IC5.4 (GND), INSTR.3, LIGHT-1.1, MAINS.1, PWR/LI-2.1, Q8.1 (S), Q8.2 (S), Q8.3 (S), R1.1, R3.2, R5.2, R13.1, STATUS.2, V-BATT.3, V-MOT.3
GREEN: R11.2, STATUS.3
INSTR-LIGHT: INSTR.2, Q8.5 (D), Q8.6 (D), Q8.7 (D), Q8.8 (D)
unnamed: Q8.4 (G), R12.1, R13.2
unnamed: +5V.C, R1.2
RED: R10.2, STATUS.1
SUPL: INSTR.1, JP1.2
VCC: +5V.A, AMP.2, BREAK.3, C14.2, C15.2, C16.+, DIR.3, DRIVE.3, IC5.3 (VO), JP1.3, LIGHT-1.3, MAINS.3, PWR/LI-2.3, R2.2, R4.2, V-BATT.2, V-MOT.2

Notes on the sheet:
LOCO-Control-Adapter V2.2

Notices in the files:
parts and their libraries:
Crystals: Copyright: Geyer-Electronic
COPYRIGHT: Copyright (C) 2023 Ultra Librarian. All rights reserved.
